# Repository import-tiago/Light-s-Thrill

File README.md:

# Light's Thrill

Light's Thrill is an USB HID controller for RGB LED-strips, compatible with Corsair iCUE application.

#### Compatible with: 
* [iCUE](https://www.corsair.com/br/pt/icue)
* [OpenRGB](https://gitlab.com/CalcProgrammer1/OpenRGB)
* [JackNet RGB Sync](https://rgbsync.com/)
* [RGB Infrared Controller](https://github.com/import-tiago/Light-s-Thrill/blob/master/Assets/RGB%20Infrared%20Controller%20Example.jpg)

## 3D Printed Enclosure
 |  | 
--- | --- | ---

## Schematic

## SETUP Parts

## MCU SETUP
- Burn the Arduino Leornado bootloader at ATmega32U4 with an Arduino UNO as ISP programmer using SPI circuit connection.
- Install the Corsair Lighting Protocol Boards to the Arduino IDE from: ```https://raw.githubusercontent.com/Legion2/CorsairLightingProtocolBoards/master/package_Legion2_CorsairLightingProtocolBoards_index.json```.
- Upload the ```Firmware\Firmware.ino``` to the ATmega32u4 as following:

- Done. The device is now ready to be recognized by Corsair iCUE application.

## Corsair iCUE SETUP
- To have the maximum (2x 89) of LEDs controlled by the iCUE, configure it as follows:

## Video - Demo
<p align="center"></p>

### Contributing
0. Give this project a :star:
1. Create an issue and describe your idea.
2. [Fork it](https://github.com/import-tiago/Light-s-Thrill/fork).
3. Create your feature branch (`git checkout -b my-new-feature`).
4. Commit your changes (`git commit -a -m "Added feature title"`).
5. Publish the branch (`git push origin my-new-feature`).
6. Create a new pull request.
7. Done! :heavy_check_mark:

### License Information
<br /><span xmlns:dct="http://purl.org/dc/terms/" property="dct:title">Light's Thrill</span> by <a xmlns:cc="http://creativecommons.org/ns#" href="https://github.com/import-tiago" property="cc:attributionName" rel="cc:attributionURL">Tiago Silva</a> is licensed under a <a rel="license" href="http://creativecommons.org/licenses/by-sa/4.0/">Creative Commons Attribution-ShareAlike 4.0 International License</a>.<br />
Based on a work at <a xmlns:dct="http://purl.org/dc/terms/" href="[Corsair Lighting Protocol](https://github.com/import-tiago/CorsairLightingProtocol)" rel="dct:source">[Corsair Lighting Protocol](https://github.com/import-tiago/CorsairLightingProtocol)</a> and <a xmlns:dct="http://purl.org/dc/terms/" href="[Open Corsair Link](https://github.com/import-tiago/OpenCorsairLink)" rel="dct:source">[Open Corsair Link](https://github.com/import-tiago/OpenCorsairLink)</a>.<br />
Permissions beyond the scope of this license may be available at <a xmlns:cc="http://creativecommons.org/ns#" href="https://twitter.com/import_tiago" rel="cc:morePermissions">tiagodepaulasilva@gmail.com</a>.

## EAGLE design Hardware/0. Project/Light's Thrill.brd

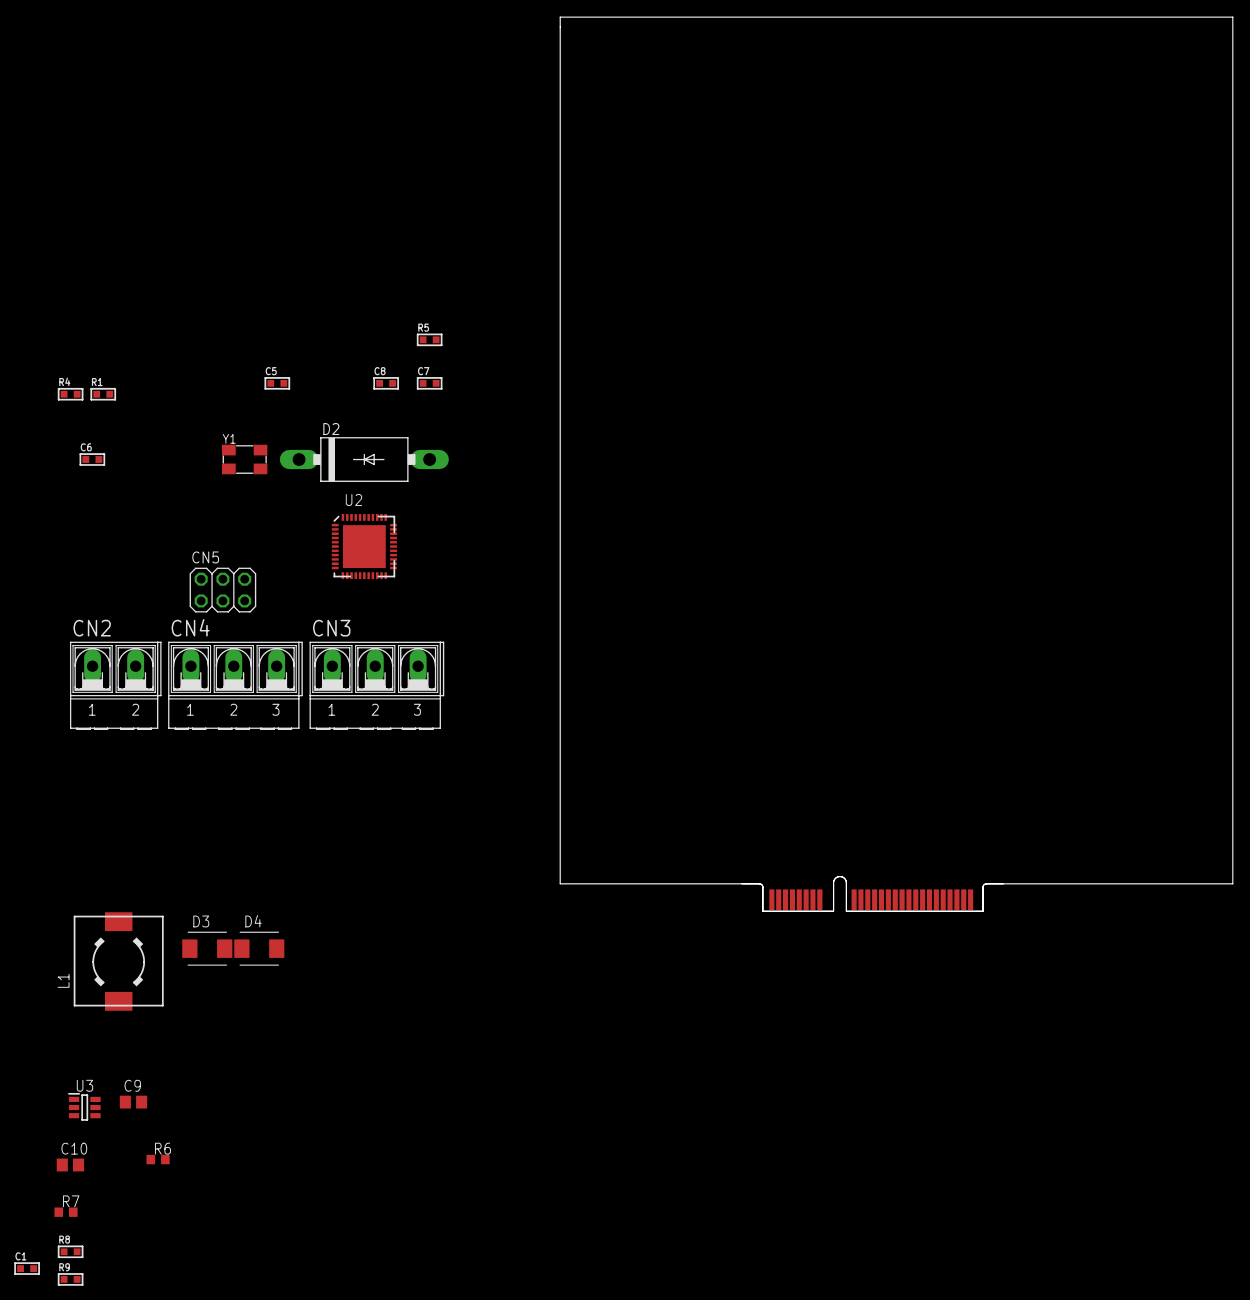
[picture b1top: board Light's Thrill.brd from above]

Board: 2 copper layers, 78.5 x 104.4 mm, 26 parts (0 on the bottom side), 25 nets, no tracks yet.

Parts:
C1, C6: 100nF; C0603
C5: 1uF; C0603
C7, C8: 22pF; C0603
C9, C10: 22uF x 16V; C0805
CN2: AK500/2-H
CN3, CN4: AK500/3-H
CN5: 2X03
CN6: mini-PCIe board connector; MINI-PCIE
D2: ER506; DO27-15
D3, D4: SS16; SMBJ
L1: 22 uH; INDUCTOR
R1: 10k (5%); R0603
R4, R5: 150R; R0603
R6: 110k (±1%); R0603
R7: 15k (±1%); R0603
R8, R9: 22R; R0603
U2: ATMEGA32U4; TESTING_QFN-44
U3: MT3608; SOT95P280X145-6N
Y1: 16MHz; 5.0X3.2_KX-9A

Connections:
0V: C1.2, C5.2, C6.2, C7.2, C8.2, C9.2, C10.2, CN2.2, CN3.3, CN4.3, CN5.6, CN6.4, CN6.9, CN6.15, CN6.18, CN6.21, CN6.26, CN6.27, CN6.29, CN6.34, CN6.35, CN6.40, CN6.50, R7.1, U2.5, U2.15, U2.23, U2.33, U2.35, U2.43, U3.2
3.3V: C1.1, C9.1, CN5.2, CN6.2, CN6.52, L1.1, U3.4, U3.5
5V: CN3.1, CN4.1, D2.C
!ICSP_RESET: CN5.5, R1.1, U2.13
+5V: D4.C, R1.2, U2.14, U2.24, U2.34, U2.44
CH1_LEDS_CONTROL: CN3.2, R4.2
CH2_LEDS_CONTROL: CN4.2, R5.2
ICSP_MISO: CN5.1, U2.8
ICSP_MOSI: CN5.4, U2.10
ICSP_SCK: CN5.3, U2.9
unnamed: D3.A, L1.2, U3.1
unnamed: R6.1, R7.2, U3.3
unnamed: R4.1, U2.18
unnamed: CN6.38, R8.1
unnamed: CN6.36, R9.1
unnamed: CN2.1, D2.A
unnamed: R5.1, U2.27
unnamed: C7.1, U2.17, Y1.1
unnamed: C8.1, U2.16, Y1.3
unnamed: C5.1, U2.6
unnamed: C6.1, U2.42
USB_D+: R8.2, U2.4
USB_D-: R9.2, U2.3
VBUS: U2.2, U2.7
V_DC-DC: C10.1, D3.C, D4.A, R6.2

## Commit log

2020-07-11 Schematic 1.0 - DONE
2020-07-11 New datasheets added
2020-07-11 Schematic preview generated
2020-07-11 readme created
2020-07-11 Schematic Preview margin removed
2020-07-12 Schematic 1.1 - DONE
    - User's interface circuit added (button and LED)
    - 12V to 5V LDO added (working without a computer)
    - External power supply circuit detect added
2020-07-12 Schematic Preview image margin removed
2020-07-12 Minimum PWM/MOSFET firmware test
2020-07-12 Schematic 1.2 - Minor improvements
2020-07-12 Schematic Preview updated to 1.2 revision
2020-07-12 Minor improvements
2020-07-12 PCB Layout 1.2 - DONE
2020-07-12 Gerbers Files - PCB 1.2
2020-07-12 Preview images added
2020-07-12 Preview images detailed
2020-07-12 Schematic + PCB 1.3 up to date
    - Change MCU_PWM_RED to a 16 bit PWM pin.
2020-07-12 Schematic image preview updated to 1.3 PCB revision
2020-07-13 Descriptive titles improved
2020-07-13 ICSP Programming added (PCB 1.4)
2020-07-13 Minimum RGB and PWM/MOSFET firmware test
2020-07-14 Minimum RGBLED Library firmware test
2020-07-15 FIRMWARE - WIP
2020-07-15 Project working properly with IR remote controller
2020-07-16 IR Controller + iCUE working properly
2020-07-16 Enclosure Preview image rendered
2020-07-16 Added used libraries
2020-07-16 RGB Infrared Controller Example image added
2020-07-17 Minor PCB improvements
2020-07-17 PCB preview image rendered
2020-07-17 .gitattributes added
2020-08-09 Video preview image added
2020-08-09 SETUP parts image added
2021-03-24 Code updated with the latest libraries versions
2021-03-24 New images added to \Assets
2021-03-24 New images and directory structure
2021-03-31 LEDs datasheet added
2021-03-31 Schamatic temporary files removed
2021-04-01 New PCIe based design init
2021-04-11 HoodLoader + Mega + CLP working properly
2023-07-21 usernames in URLs updated

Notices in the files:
parts and their libraries:
My-RLC: Copyright (C) 2007, Bob Starr
crystal-geyer_V1_0: Copyright: Geyer-Electronic
